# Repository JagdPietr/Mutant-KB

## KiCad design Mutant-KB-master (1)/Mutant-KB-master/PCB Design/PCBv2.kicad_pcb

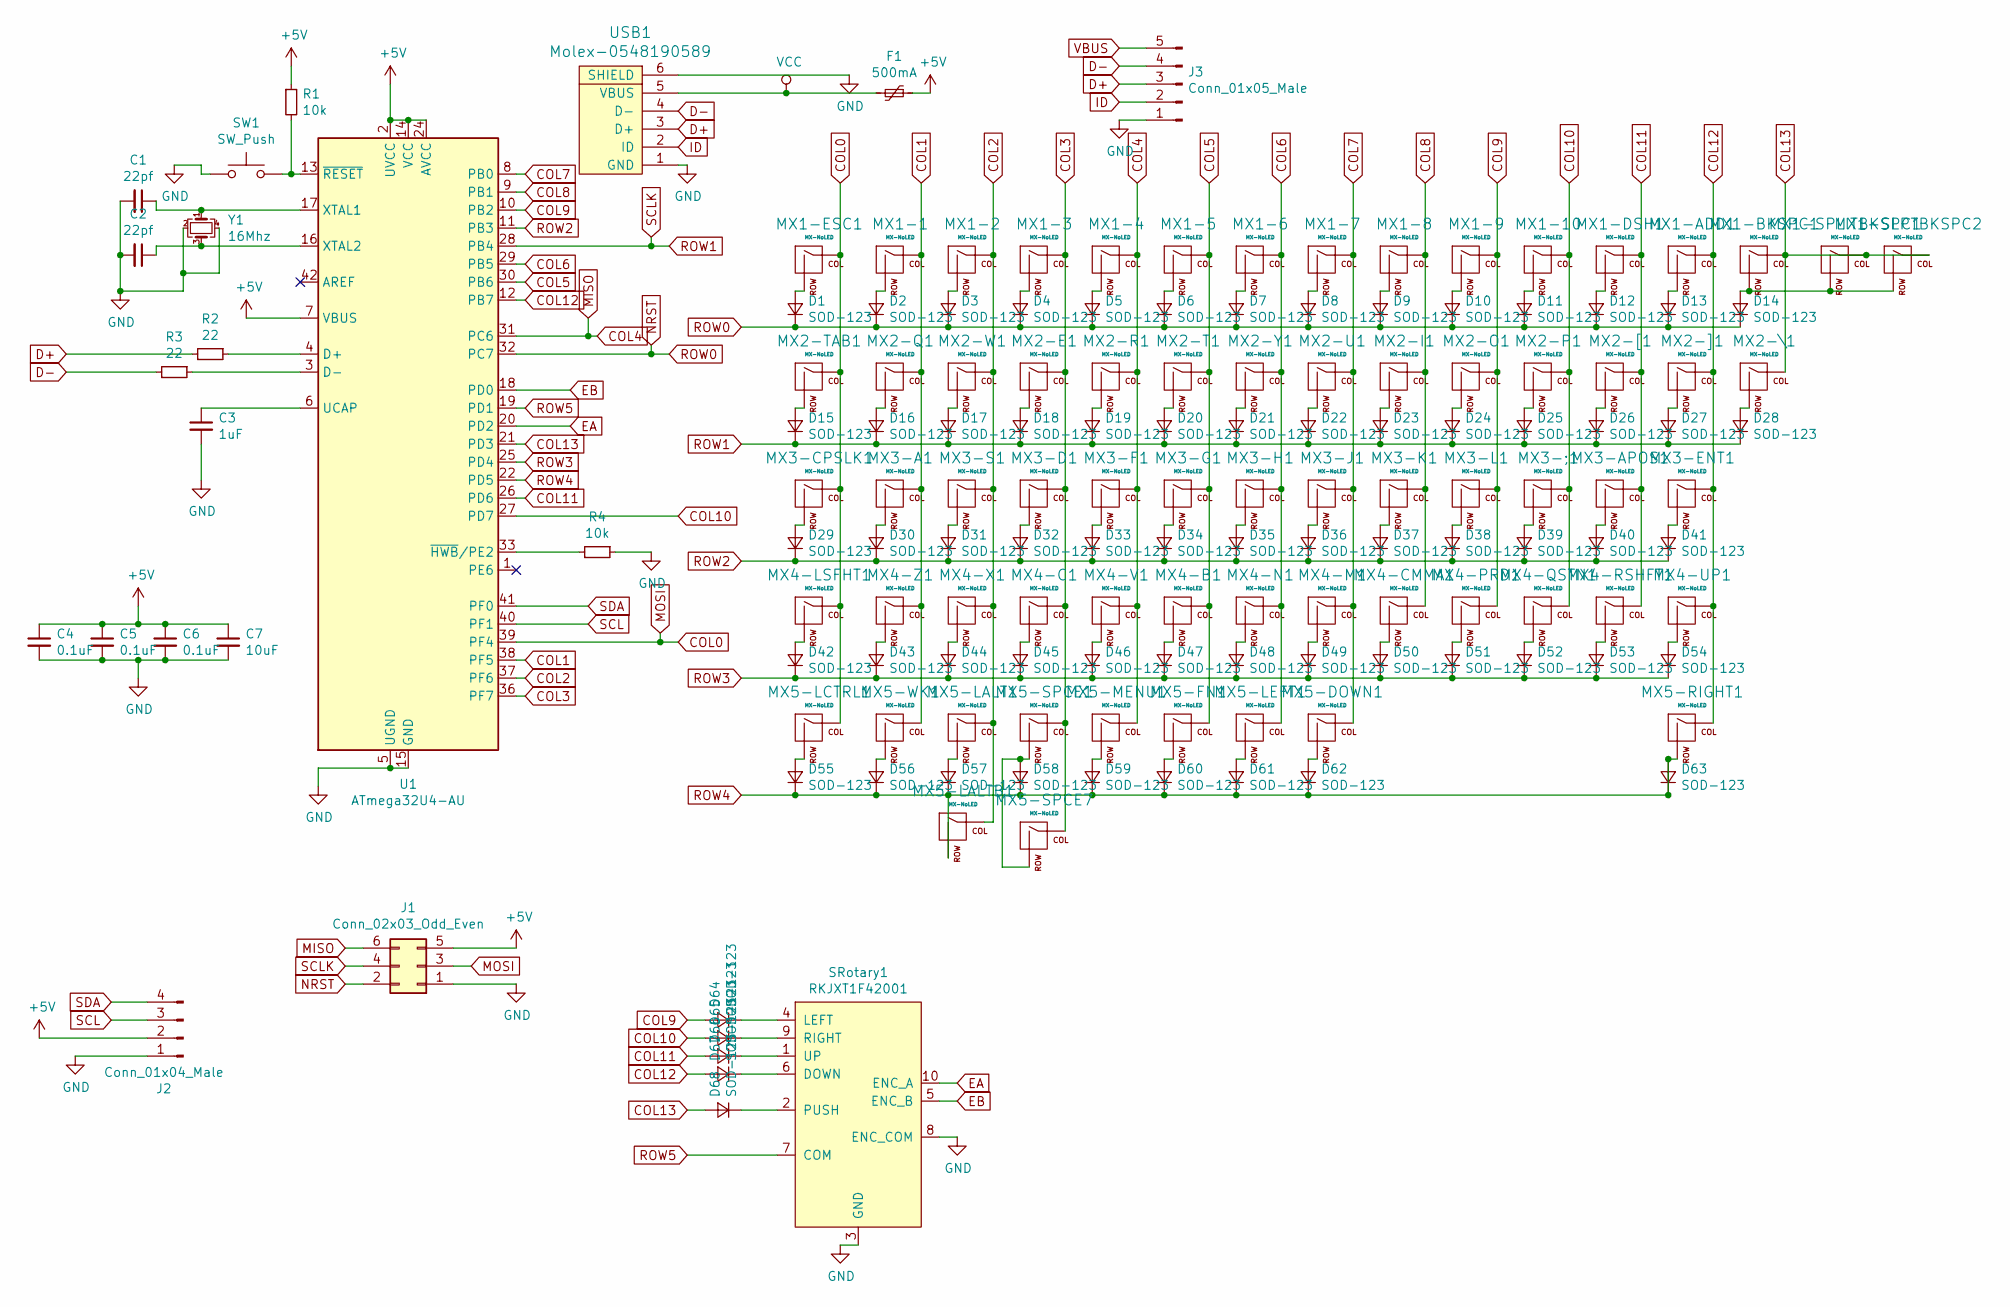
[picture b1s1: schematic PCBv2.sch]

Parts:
C1, C2: 22pf; C_0805_2012Metric
C3: 1uF; C_0805_2012Metric
C4, C5, C6: 0.1uF; C_0805_2012Metric
C7: 10uF; C_0805_2012Metric
D1, D2, D3, D4, D5, D6, D7, D8, D9, D10, D11, D12, D13, D14, D15, D16, D17, D18, D19, D20, D21, D22, D23, D24, D25, D26, D27, D28, D29, D30, D31, D32, D33, D34, D35, D36, D37, D38, D39, D40, D41, D42, D43, D44, D45, D46, D47, D48, D49, D50, D51, D52, D53, D54, D55, D56, D57, D58, D59, D60, D61, D62, D63, D64, D65, D66, D67, D68: SOD-123; D_SOD-123
F1: 500mA; Fuse_1206_3216Metric
J1: Conn_02x03_Odd_Even; PinSocket_2x03_P2.54mm_Vertical
J2: Conn_01x04_Male; PinHeader_1x04_P2.54mm_Vertical
J3: Conn_01x05_Male; PinHeader_1x05_P2.54mm_Vertical
MX1-1, MX1-2, MX1-3, MX1-4, MX1-5, MX1-6, MX1-7, MX1-8, MX1-9, MX1-10, MX1-ADD1, MX1-DSH1, MX1-ESC1, MX1-SLPTBKSPC2, MX1-SPLITBKSPC1, MX2-E1, MX2-I1, MX2-O1, MX2-P1, MX2-Q1, MX2-R1, MX2-T1, MX2-U1, MX2-W1, MX2-Y1, MX2-[1, MX2-]1, MX3-;1, MX3-A1, MX3-APOS1, MX3-D1, MX3-F1, MX3-G1, MX3-H1, MX3-J1, MX3-K1, MX3-L1, MX3-S1, MX4-B1, MX4-C1, MX4-CMMA1, MX4-M1, MX4-N1, MX4-PRD1, MX4-QSTN1, MX4-UP1, MX4-V1, MX4-X1, MX4-Z1, MX5-DOWN1, MX5-LEFT1, MX5-RIGHT1: MX-NoLED; MXOnly-1U-NoLED
MX1-BKSPC1: MX-NoLED; MXOnly-2U-NoLED
MX2-TAB1, MX2-\1: MX-NoLED; MXOnly-1.5U-NoLED
MX3-CPSLK1: MX-NoLED; MXOnly-1.75U-NoLED
MX3-ENT1, MX4-LSFHT1: MX-NoLED; MXOnly-2.25U-NoLED
MX4-RSHFT1, MX5-FN1, MX5-LALT1, MX5-LALTB1, MX5-LCTRL1, MX5-MENU1, MX5-WK1: MX-NoLED; MXOnly-1.25U-NoLED
MX5-SPCE1: MX-NoLED; MXOnly-6.25U-ReversedStabilizers-NoLED
MX5-SPCE7: MX-NoLED; MXOnly-7U-ReversedStabilizers-NoLED
R1, R4: 10k; R_0805_2012Metric
R2, R3: 22; R_0805_2012Metric
SRotary1: RKJXT1F42001
SW1: SW_Push; SKQG-1155865
U1: ATmega32U4-AU; TQFP-44_10x10mm_P0.8mm
USB1: Molex-0548190589
Y1: 16Mhz; Crystal_SMD_3225-4Pin_3.2x2.5mm

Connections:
+5V: C4.1, C5.1, C6.1, C7.1, F1.1, J1.5, J2.2, R1.1, U1.2 (UVCC), U1.7 (VBUS), U1.14 (VCC), U1.24 (AVCC), U1.34 (VCC), U1.44 (AVCC)
COL0: J1.3, MX1-ESC1.1 (COL), MX2-TAB1.1 (COL), MX3-CPSLK1.1 (COL), MX4-LSFHT1.1 (COL), MX5-LCTRL1.1 (COL), U1.39 (PF4)
COL1: MX1-1.1 (COL), MX2-Q1.1 (COL), MX3-A1.1 (COL), MX4-Z1.1 (COL), MX5-WK1.1 (COL), U1.38 (PF5)
COL2: MX1-2.1 (COL), MX2-W1.1 (COL), MX3-S1.1 (COL), MX4-X1.1 (COL), MX5-LALT1.1 (COL), MX5-LALTB1.1 (COL), U1.37 (PF6)
COL3: MX1-3.1 (COL), MX2-E1.1 (COL), MX3-D1.1 (COL), MX4-C1.1 (COL), MX5-SPCE1.1 (COL), MX5-SPCE7.1 (COL), U1.36 (PF7)
COL4: J1.6, MX1-4.1 (COL), MX2-R1.1 (COL), MX3-F1.1 (COL), MX4-V1.1 (COL), MX5-MENU1.1 (COL), U1.31 (PC6)
COL5: MX1-5.1 (COL), MX2-T1.1 (COL), MX3-G1.1 (COL), MX4-B1.1 (COL), MX5-FN1.1 (COL), U1.30 (PB6)
COL6: MX1-6.1 (COL), MX2-Y1.1 (COL), MX3-H1.1 (COL), MX4-N1.1 (COL), MX5-LEFT1.1 (COL), U1.29 (PB5)
COL7: MX1-7.1 (COL), MX2-U1.1 (COL), MX3-J1.1 (COL), MX4-M1.1 (COL), MX5-DOWN1.1 (COL), U1.8 (PB0)
COL9: D64.2 (A), MX1-9.1 (COL), MX2-O1.1 (COL), MX3-L1.1 (COL), MX4-PRD1.1 (COL), U1.10 (PB2)
COL10: D65.2 (A), MX1-10.1 (COL), MX2-P1.1 (COL), MX3-;1.1 (COL), MX4-QSTN1.1 (COL), U1.27 (PD7)
COL11: D66.2 (A), MX1-DSH1.1 (COL), MX2-[1.1 (COL), MX3-APOS1.1 (COL), MX4-RSHFT1.1 (COL), U1.26 (PD6)
COL13: D68.2 (A), MX1-BKSPC1.1 (COL), MX1-SLPTBKSPC2.1 (COL), MX1-SPLITBKSPC1.1 (COL), MX2-\1.1 (COL), U1.21 (PD3)
D+: J3.3, R2.2, USB1.3 (D+)
D-: J3.4, R3.2, USB1.4 (D-)
EA: SRotary1.10 (ENC_A), U1.20 (PD2)
EB: SRotary1.5 (ENC_B), U1.18 (PD0)
GND: C1.2, C2.2, C3.2, C4.2, C5.2, C6.2, C7.2, J1.1, J2.1, J3.1, R4.1, SRotary1.3 (GND), SRotary1.8 (ENC_COM), SW1.1, U1.5 (UGND), U1.15 (GND), U1.23 (GND), U1.35 (GND), U1.43 (GND), USB1.1 (GND), USB1.6 (SHIELD), Y1.2, Y1.4
NRST: D1.1 (K), D2.1 (K), D3.1 (K), D4.1 (K), D5.1 (K), D6.1 (K), D7.1 (K), D8.1 (K), D9.1 (K), D10.1 (K), D11.1 (K), D12.1 (K), D13.1 (K), D14.1 (K), J1.2, U1.32 (PC7)
unnamed: C1.1, U1.17 (XTAL1), Y1.1
unnamed: C2.1, U1.16 (XTAL2), Y1.3
unnamed: C3.1, U1.6 (UCAP)
unnamed: D1.2 (A), MX1-ESC1.2 (ROW)
unnamed: D2.2 (A), MX1-1.2 (ROW)
unnamed: D3.2 (A), MX1-2.2 (ROW)
unnamed: D4.2 (A), MX1-3.2 (ROW)
unnamed: D5.2 (A), MX1-4.2 (ROW)
unnamed: D6.2 (A), MX1-5.2 (ROW)
unnamed: D7.2 (A), MX1-6.2 (ROW)
unnamed: D8.2 (A), MX1-7.2 (ROW)
unnamed: D9.2 (A), MX1-8.2 (ROW)
unnamed: D10.2 (A), MX1-9.2 (ROW)
unnamed: D11.2 (A), MX1-10.2 (ROW)
unnamed: D12.2 (A), MX1-DSH1.2 (ROW)
unnamed: D13.2 (A), MX1-ADD1.2 (ROW)
unnamed: D14.2 (A), MX1-BKSPC1.2 (ROW), MX1-SLPTBKSPC2.2 (ROW), MX1-SPLITBKSPC1.2 (ROW)
unnamed: D15.2 (A), MX2-TAB1.2 (ROW)
unnamed: D16.2 (A), MX2-Q1.2 (ROW)
unnamed: D17.2 (A), MX2-W1.2 (ROW)
unnamed: D18.2 (A), MX2-E1.2 (ROW)
unnamed: D19.2 (A), MX2-R1.2 (ROW)
unnamed: D20.2 (A), MX2-T1.2 (ROW)
unnamed: D21.2 (A), MX2-Y1.2 (ROW)
unnamed: D22.2 (A), MX2-U1.2 (ROW)
unnamed: D23.2 (A), MX2-I1.2 (ROW)
unnamed: D24.2 (A), MX2-O1.2 (ROW)
unnamed: D25.2 (A), MX2-P1.2 (ROW)
unnamed: D26.2 (A), MX2-[1.2 (ROW)
unnamed: D27.2 (A), MX2-]1.2 (ROW)
unnamed: D28.2 (A), MX2-\1.2 (ROW)
unnamed: D29.2 (A), MX3-CPSLK1.2 (ROW)
unnamed: D30.2 (A), MX3-A1.2 (ROW)
unnamed: D31.2 (A), MX3-S1.2 (ROW)
unnamed: D32.2 (A), MX3-D1.2 (ROW)
unnamed: D33.2 (A), MX3-F1.2 (ROW)
unnamed: D34.2 (A), MX3-G1.2 (ROW)
unnamed: D35.2 (A), MX3-H1.2 (ROW)
unnamed: D36.2 (A), MX3-J1.2 (ROW)
unnamed: D37.2 (A), MX3-K1.2 (ROW)
unnamed: D38.2 (A), MX3-L1.2 (ROW)
unnamed: D39.2 (A), MX3-;1.2 (ROW)
unnamed: D40.2 (A), MX3-APOS1.2 (ROW)
unnamed: D41.2 (A), MX3-ENT1.2 (ROW)
unnamed: D42.2 (A), MX4-LSFHT1.2 (ROW)
unnamed: D43.2 (A), MX4-Z1.2 (ROW)
unnamed: D44.2 (A), MX4-X1.2 (ROW)
unnamed: D45.2 (A), MX4-C1.2 (ROW)
unnamed: D46.2 (A), MX4-V1.2 (ROW)
unnamed: D47.2 (A), MX4-B1.2 (ROW)
unnamed: D48.2 (A), MX4-N1.2 (ROW)
unnamed: D49.2 (A), MX4-M1.2 (ROW)
unnamed: D50.2 (A), MX4-CMMA1.2 (ROW)
unnamed: D51.2 (A), MX4-PRD1.2 (ROW)
unnamed: D52.2 (A), MX4-QSTN1.2 (ROW)
unnamed: D53.2 (A), MX4-RSHFT1.2 (ROW)
unnamed: D54.2 (A), MX4-UP1.2 (ROW)
unnamed: D55.2 (A), MX5-LCTRL1.2 (ROW)
unnamed: D56.2 (A), MX5-WK1.2 (ROW)
unnamed: D57.2 (A), MX5-LALT1.2 (ROW)
unnamed: D58.2 (A), MX5-SPCE1.2 (ROW), MX5-SPCE7.2 (ROW)
unnamed: D59.2 (A), MX5-MENU1.2 (ROW)
unnamed: D60.2 (A), MX5-FN1.2 (ROW)
unnamed: D61.2 (A), MX5-LEFT1.2 (ROW)
unnamed: D62.2 (A), MX5-DOWN1.2 (ROW)
unnamed: D64.1 (K), SRotary1.4 (LEFT)
unnamed: D65.1 (K), SRotary1.9 (RIGHT)
unnamed: D66.1 (K), SRotary1.1 (UP)
unnamed: D67.1 (K), SRotary1.6 (DOWN)
unnamed: D68.1 (K), SRotary1.2 (PUSH)
unnamed: R1.2, SW1.2, U1.13 (~RESET)
unnamed: R2.1, U1.4 (D+)
unnamed: R3.1, U1.3 (D-)
unnamed: R4.2, U1.33 (~HWB~/PE2)
unnamed: J3.2, USB1.2 (ID)
ROW1: D15.1 (K), D16.1 (K), D17.1 (K), D18.1 (K), D19.1 (K), D20.1 (K), D21.1 (K), D22.1 (K), D23.1 (K), D24.1 (K), D25.1 (K), D26.1 (K), D27.1 (K), D28.1 (K), J1.4, U1.28 (PB4)
ROW2: D29.1 (K), D30.1 (K), D31.1 (K), D32.1 (K), D33.1 (K), D34.1 (K), D35.1 (K), D36.1 (K), D37.1 (K), D38.1 (K), D39.1 (K), D40.1 (K), D41.1 (K), U1.11 (PB3)
ROW3: D42.1 (K), D43.1 (K), D44.1 (K), D45.1 (K), D46.1 (K), D47.1 (K), D48.1 (K), D49.1 (K), D50.1 (K), D51.1 (K), D52.1 (K), D53.1 (K), D54.1 (K), U1.25 (PD4)
ROW5: SRotary1.7 (COM), U1.19 (PD1)
SCL: J2.3, U1.40 (PF1)
SDA: J2.4, U1.41 (PF0)
VCC: F1.2, USB1.5 (VBUS)

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
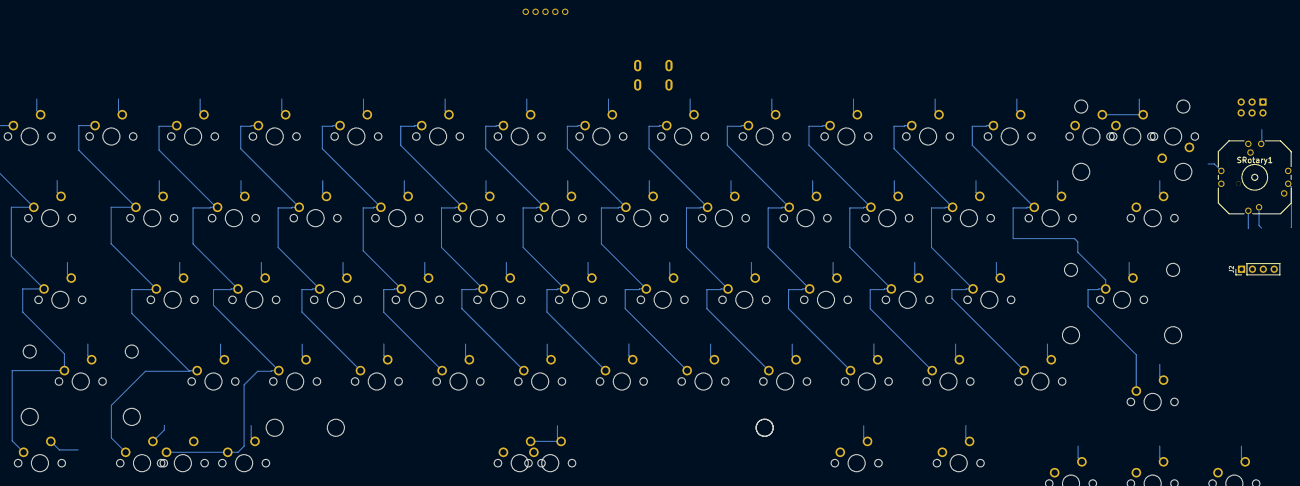
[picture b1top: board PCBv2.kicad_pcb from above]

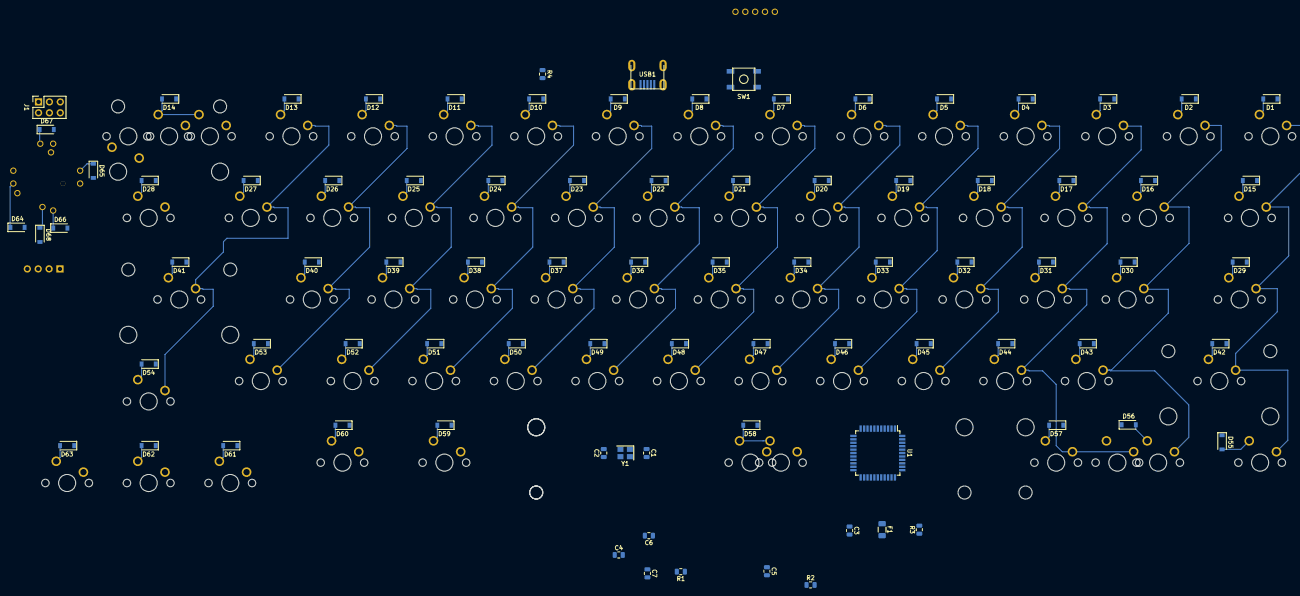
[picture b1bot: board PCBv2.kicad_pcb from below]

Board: 2 copper layers, 159 parts (85 on the bottom side), 104 nets.

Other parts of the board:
D+: MountingHole_1.5mm; MountingHole_2.1mm
D-: MountingHole_1.5mm; MountingHole_2.1mm
GND: MountingHole_1.5mm; MountingHole_2.1mm
ID: MountingHole_1.5mm; MountingHole_2.1mm
VBUS/VCC: MountingHole_1.5mm; MountingHole_2.1mm

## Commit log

2020-03-21 Add submodules
2020-03-21 Libraries
2020-03-21 Added Libraries
2020-03-21 PCB Schematics
2020-03-21 PCB Edits
2020-03-21 COL-ROW Routing
2020-03-23 Switch layout edit
2020-03-23 Added Layout Edits
2020-03-23 Update fp-info-cache
2020-03-23 Other Parts
2020-03-23 Additional Lib and parts
2020-03-23 Added Footprints
2020-03-23 PCB Prep
2020-03-24 Layout Designing
2020-03-24 Layout Edits
2020-03-24 Routing
2020-03-24 Update Mutant-KB
2020-03-24 PCB Color
2020-03-25 Added ISP Connector
2020-03-25 Update PCB Design.sch-bak
2020-03-25 Gerbers
2020-03-27 Updates (PCB, Annotation)
2020-03-29 Layout Updates
2020-03-31 Plate Updates
2020-03-31 Updates - Final Version (added usb-c daughterboard support)
